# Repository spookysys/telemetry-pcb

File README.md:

# A brain for my rocket

## Features 

* Arduino-compatible
* Adafruit Feather M0 firmware and pinout
* Small size - fits the smallest model rockets (e.g. 26mm diameter)
* Fairly powerful MCU (Atmel ARM M0 at 32MHz)
* GSM/GPRS for telemetry (SIM868)
* GPS for positioning (SIM868)
* 9-DOF Inertial Motion Unit (MPU-9259)
* Altimeter (BMP-280)
* MicroSD for logging
* Integrated usb-port, lipo-charger and power switch

## Adafruit Feather compatibility

* Same pinout as Adafruit Feather M0. An on-board component interfers with D5 (see note).
* MicroSD wired similar to Adalogger M0, but chip-select is on D7 not D4
* Voltage is 3.0 instead of 3.3
* I2C pull-ups are present

Note: If you don't need hardware handshaking on the GSM UART, the D5 pin can be freed up by cutting JP2 on the back of the board.

## Status

Testing in progress

## Credit

Design derived from Adafruit M0 Feather Proto and Adalogger

Adafruit invests time and resources providing this open source design, 
please support Adafruit and open-source hardware by purchasing 
products from Adafruit!

Creative Commons Attribution, Share-Alike license, check license.txt for more information
All text above must be included in any redistribution

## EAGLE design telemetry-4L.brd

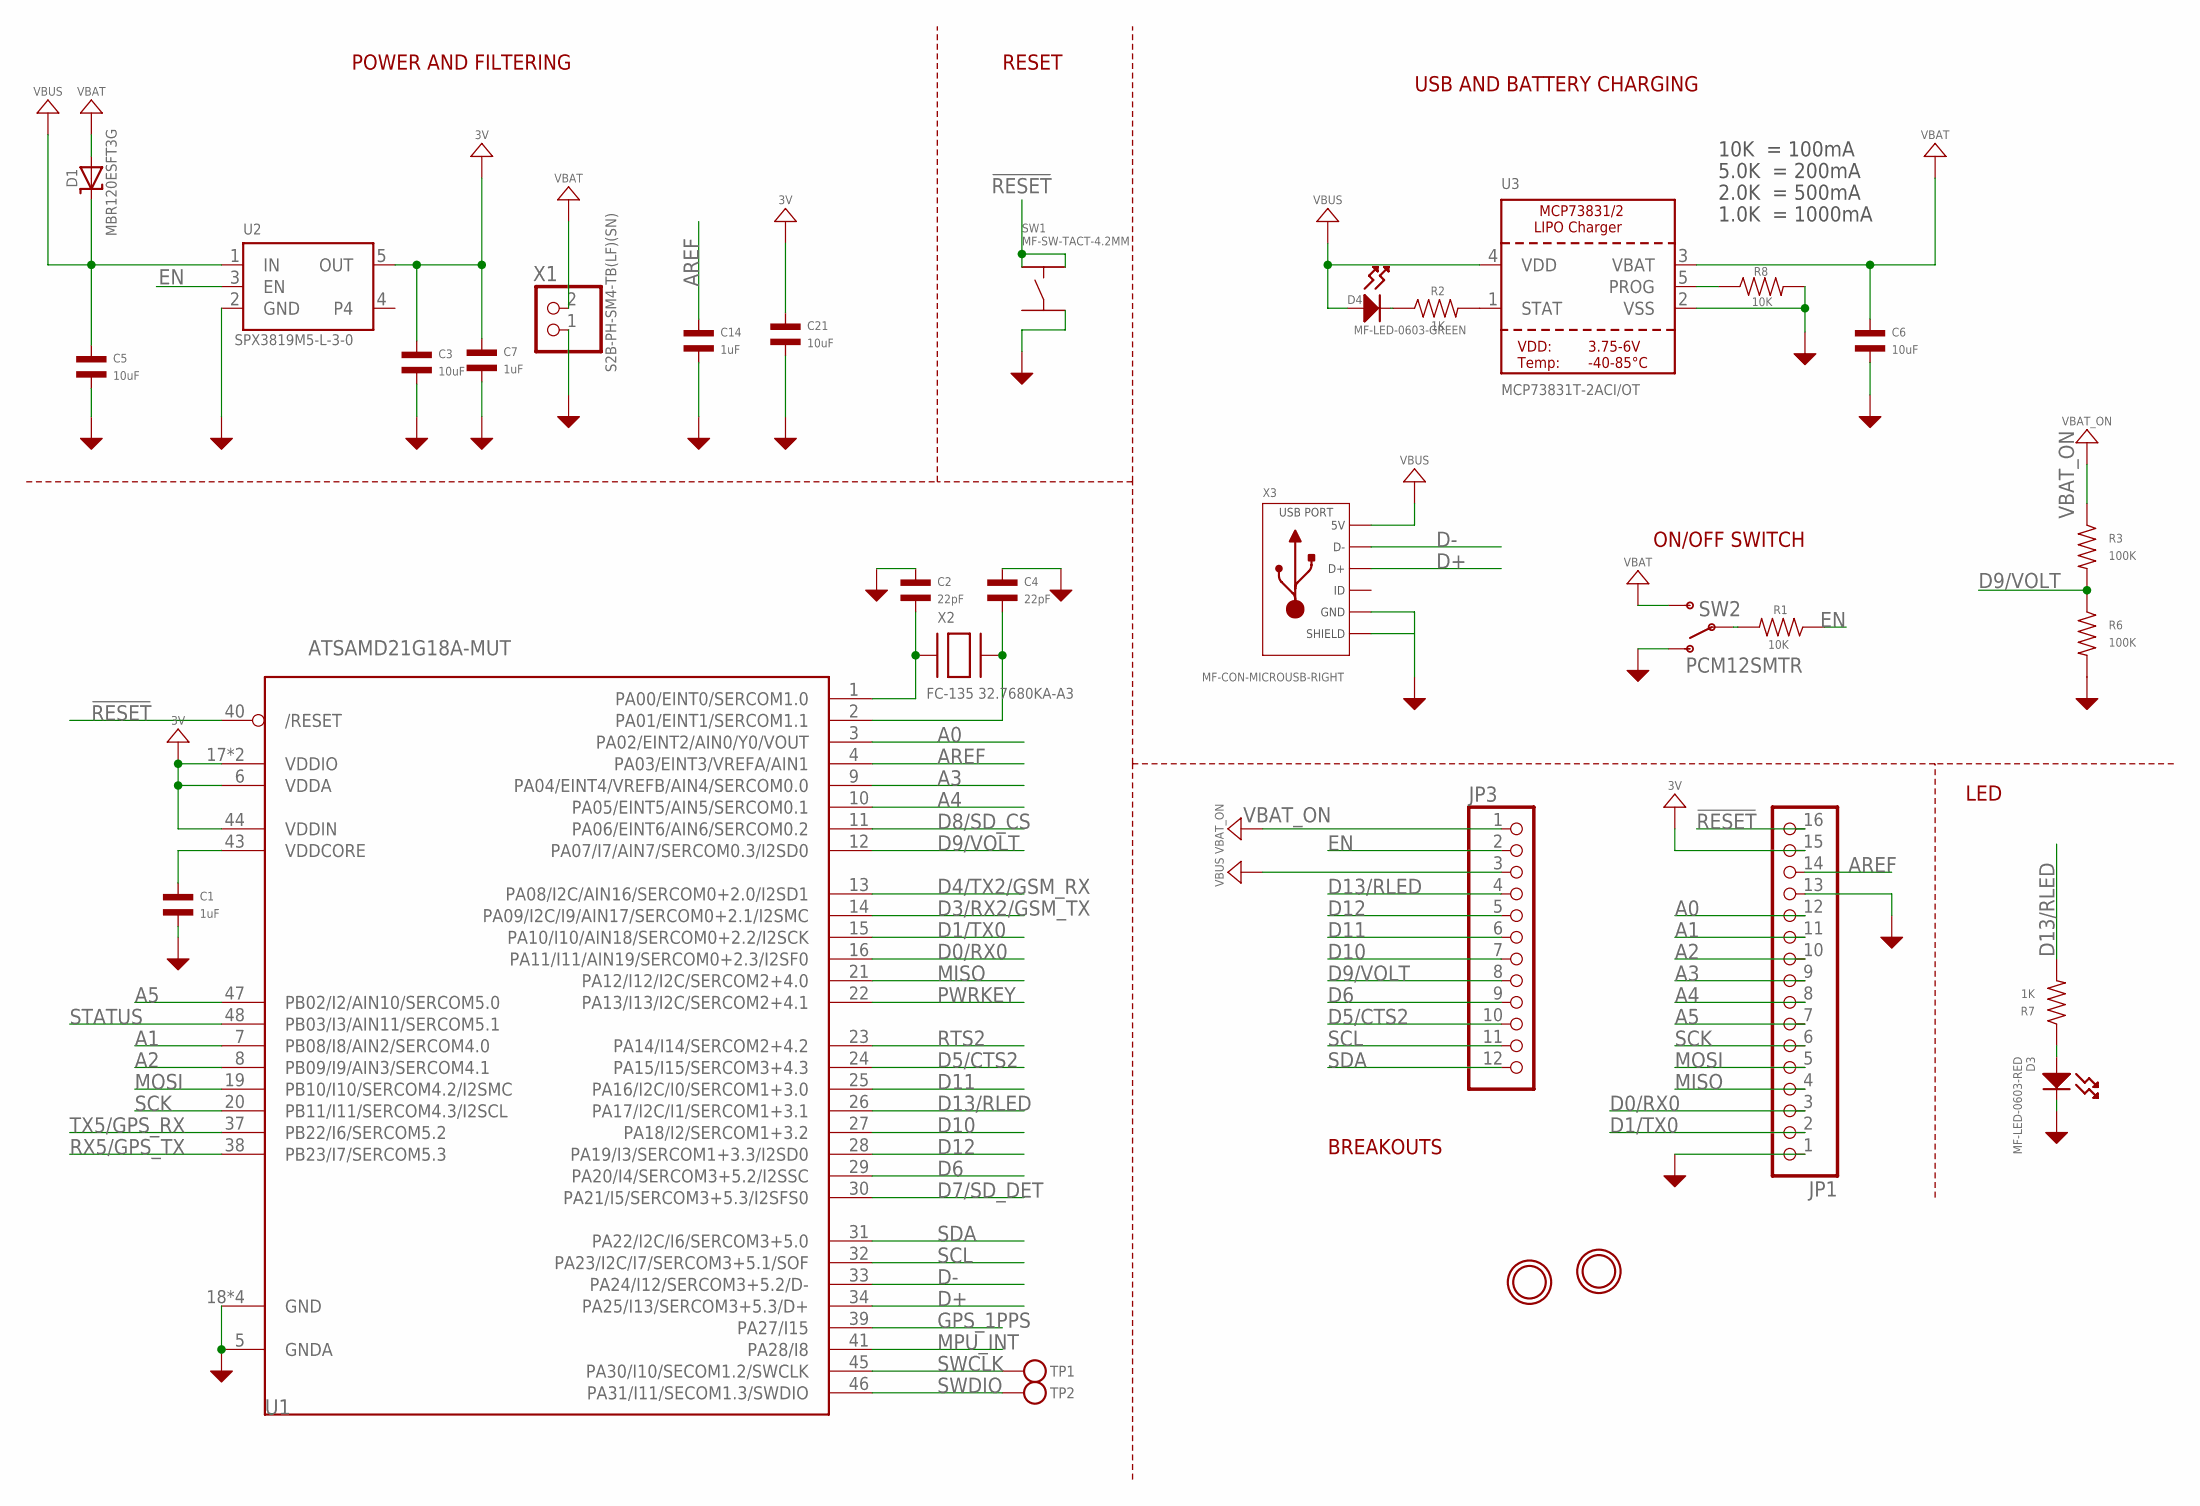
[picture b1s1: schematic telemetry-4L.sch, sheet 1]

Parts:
C1, C7, C14: 1uF; C0402
C2, C4: 22pF; C0402
C3, C5, C6, C21: 10uF; C0603; MPN GRM188R60J106ME47D
D1: MBR120ESFT3G; SOD-123
D3: MF-LED-0603-RED; LED0603
D4: MF-LED-0603-GREEN; LED0603
JP1: HEADER-1X16ROUND; 1X16_ROUND
JP3: HEADER-1X12; 1X12_ROUND
R1, R8: 10K; R0402
R2, R7: 1K; R0402
R3, R6: 100K; R0402
SW1: MF-SW-TACT-4.2MM; TACT4.2MM
SW2: PCM12SMTR; KPS-1290
TP1, TP2: TESTPOINTROUND1.5MM; TESTPOINT_ROUND_1.5MM
U1: ATSAMD21G18A-MUT; TQFN48_7MM
U2: SPX3819M5-L-3-0; SOT23-5
U3: MCP73831T-2ACI/OT; SOT23-5
U$31, U$32: MOUNTINGHOLE2.5; MOUNTINGHOLE_2.5_PLATED
X1: S2B-PH-SM4-TB(LF)(SN); JSTPH2
X2: FC-135 32.7680KA-A3; XTAL3215
X3: MF-CON-MICROUSB-RIGHT; MICROUSB-RIGHT

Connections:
!RESET: JP1.16, SW1.P$1, SW1.P$2, U1.40 (/RESET)
+3V: C3.P$1, C7.P$1, C21.P$1, JP1.15, U1.6 (VDDA), U1.17 (VDDIO), U1.36 (VDDIO), U1.44 (VDDIN), U2.5 (OUT); also elsewhere on the board
A0: JP1.12, U1.3 (PA02/EINT2/AIN0/Y0/VOUT)
A1: JP1.11, U1.7 (PB08/I8/AIN2/SERCOM4.0)
A2: JP1.10, U1.8 (PB09/I9/AIN3/SERCOM4.1)
A3: JP1.9, U1.9 (PA04/EINT4/VREFB/AIN4/SERCOM0.0)
A4: JP1.8, U1.10 (PA05/EINT5/AIN5/SERCOM0.1)
A5: JP1.7, U1.47 (PB02/I2/AIN10/SERCOM5.0)
AREF: C14.P$1, JP1.14, U1.4 (PA03/EINT3/VREFA/AIN1)
D0/RX0: JP1.3, U1.16 (PA11/I11/AIN19/SERCOM0+2.3/I2SF0)
D1/TX0: JP1.2, U1.15 (PA10/I10/AIN18/SERCOM0+2.2/I2SCK)
D3/RX2/GSM_TX: U1.14 (PA09/I2C/I9/AIN17/SERCOM0+2.1/I2SMC); also elsewhere on the board
D4/TX2/GSM_RX: U1.13 (PA08/I2C/AIN16/SERCOM0+2.0/I2SD1); also elsewhere on the board
D5/CTS2: JP3.10, U1.24 (PA15/I15/SERCOM3+4.3); also elsewhere on the board
D6: JP3.9, U1.29 (PA20/I4/SERCOM3+5.2/I2SSC)
D7/SD_DET: U1.30 (PA21/I5/SERCOM3+5.3/I2SFS0); also elsewhere on the board
D8/SD_CS: U1.11 (PA06/EINT6/AIN6/SERCOM0.2); also elsewhere on the board
D9/VOLT: JP3.8, R3.P$2, R6.P$1, U1.12 (PA07/I7/AIN7/SERCOM0.3/I2SD0)
D10: JP3.7, U1.27 (PA18/I2/SERCOM1+3.2)
D11: JP3.6, U1.25 (PA16/I2C/I0/SERCOM1+3.0)
D12: JP3.5, U1.28 (PA19/I3/SERCOM1+3.3/I2SD0)
D13/RLED: JP3.4, R7.P$2, U1.26 (PA17/I2C/I1/SERCOM1+3.1)
D+: U1.34 (PA25/I13/SERCOM3+5.3/D+), X3.3 (D+)
D-: U1.33 (PA24/I12/SERCOM3+5.2/D-), X3.2 (D-)
EN: JP3.2, R1.P$1, U2.3 (EN); also elsewhere on the board
GND: C1.P$2, C2.P$1, C3.P$2, C4.P$1, C5.P$2, C6.P$2, C7.P$2, C14.P$2, C21.P$2, D3.CATHODE, JP1.1, JP1.13, R6.P$2, R8.P$2, SW1.P$4, SW2.O, U1.5 (GNDA), U1.18 (GND), U1.35 (GND), U1.42 (GND), U1.THERMAL (GND), U2.2 (GND), U3.2 (VSS), X1.1, X3.5 (GND), X3.S1 (SLD), X3.S2 (SLD), X3.S3 (SLD), X3.S4 (SLD), X3.S5 (SLD), X3.S6 (SLD); also elsewhere on the board
GPS_1PPS: U1.39 (PA27/I15); also elsewhere on the board
MISO: JP1.4, U1.21 (PA12/I12/I2C/SERCOM2+4.0); also elsewhere on the board
MOSI: JP1.5, U1.19 (PB10/I10/SERCOM4.2/I2SMC); also elsewhere on the board
MPU_INT: U1.41 (PA28/I8); also elsewhere on the board
unnamed: D4.CATHODE, R2.P$1
unnamed: R2.P$2, U3.1 (STAT)
unnamed: R8.P$1, U3.5 (PROG)
unnamed: C2.P$2, U1.1 (PA00/EINT0/SERCOM1.0), X2.P$1
unnamed: C4.P$2, U1.2 (PA01/EINT1/SERCOM1.1), X2.P$2
unnamed: D3.ANODE, R7.P$1
unnamed: R1.P$2, SW2.P
PWRKEY: U1.22 (PA13/I13/I2C/SERCOM2+4.1); also elsewhere on the board
RTS2: U1.23 (PA14/I14/SERCOM2+4.2); also elsewhere on the board
RX5/GPS_TX: U1.38 (PB23/I7/SERCOM5.3); also elsewhere on the board
SCK: JP1.6, U1.20 (PB11/I11/SERCOM4.3/I2SCL); also elsewhere on the board
SCL: JP3.11, U1.32 (PA23/I2C/I7/SERCOM3+5.1/SOF); also elsewhere on the board
SDA: JP3.12, U1.31 (PA22/I2C/I6/SERCOM3+5.0); also elsewhere on the board
STATUS: U1.48 (PB03/I3/AIN11/SERCOM5.1); also elsewhere on the board
SWCLK: TP1.P$1, U1.45 (PA30/I10/SECOM1.2/SWCLK); also elsewhere on the board
SWDIO: TP2.P$1, U1.46 (PA31/I11/SECOM1.3/SWDIO)
TX5/GPS_RX: U1.37 (PB22/I6/SERCOM5.2); also elsewhere on the board
VBAT: C6.P$1, D1.A, SW2.S, U3.3 (VBAT), X1.2; also elsewhere on the board
VBAT_ON: JP3.1, R3.P$1; also elsewhere on the board
VBUS: C5.P$1, D1.C, D4.ANODE, JP3.3, U2.1 (IN), U3.4 (VDD), X3.1 (5V)
VDDCORE: C1.P$1, U1.43 (VDDCORE)

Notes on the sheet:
POWER AND FILTERING
RESET
10K = 100mA
5.0K = 200mA
2.0K = 500mA
1.0K = 1000mA
USB AND BATTERY CHARGING
BREAKOUTS
LED
ON/OFF SWITCH

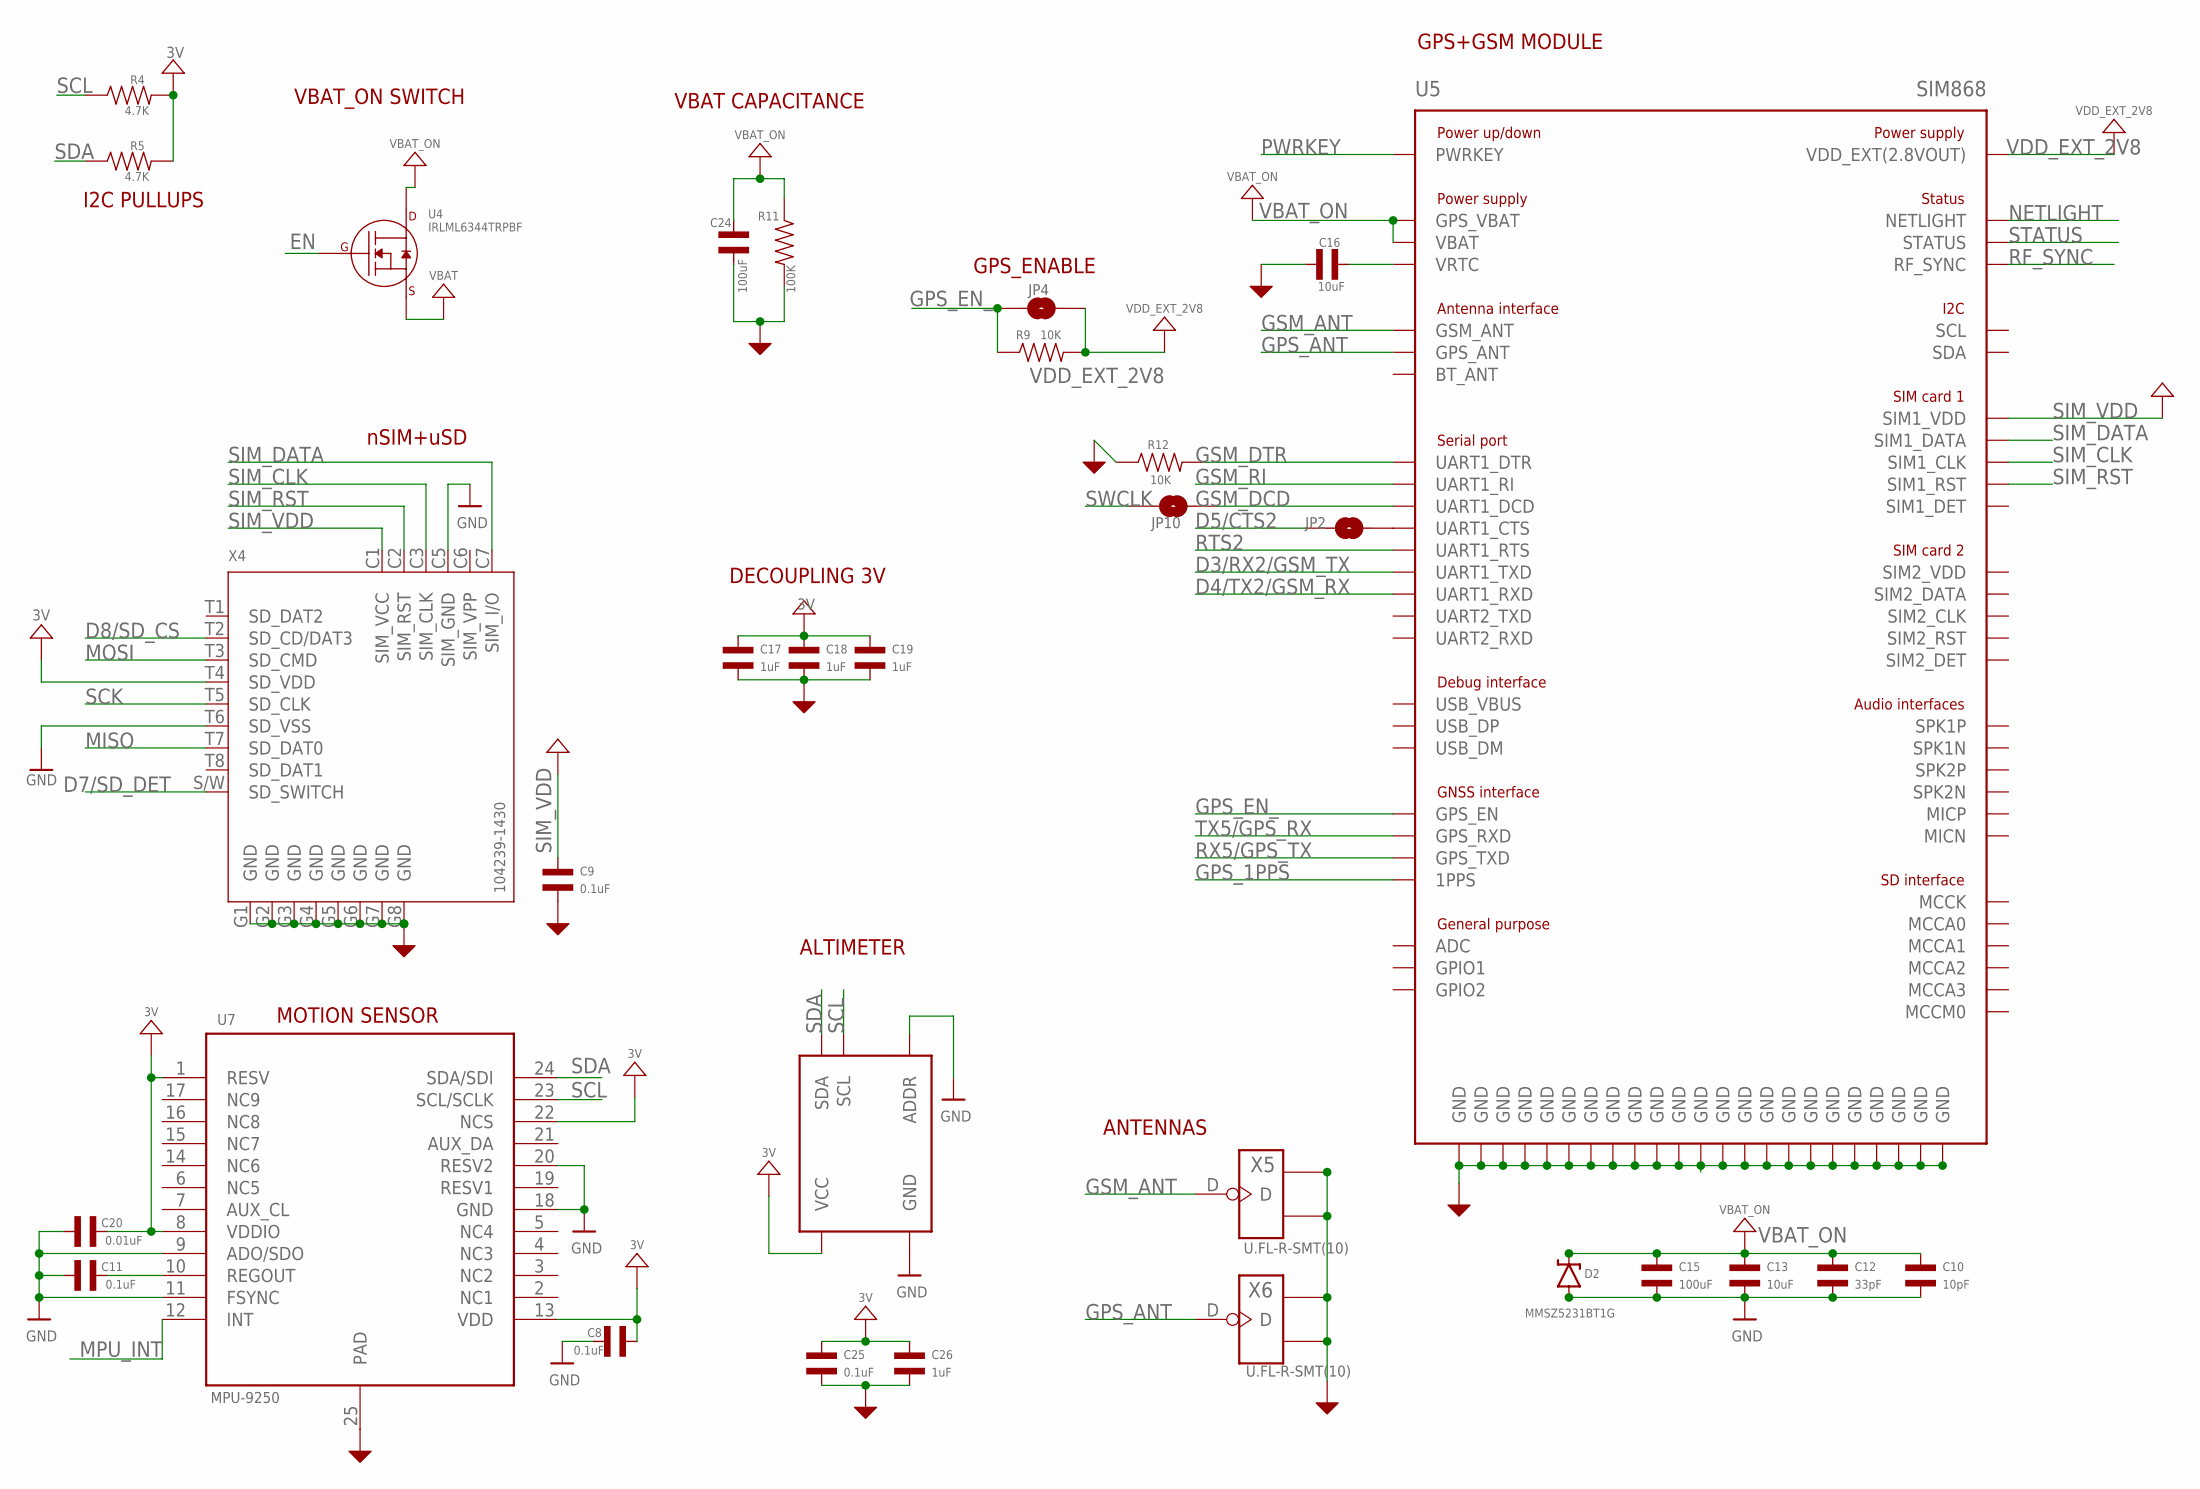
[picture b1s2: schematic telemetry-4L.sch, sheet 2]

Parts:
C8, C9, C11, C25: 0.1uF; C0402
C10: 10pF; C0402; MPN GRM1555C1H100JA01J
C12: 33pF; C0402; MPN GRM1555C1H330JA01D
C13, C16: 10uF; C0603; MPN GRM188R60J106ME47D
C15, C24: 100uF; C1206; MPN CL31A107MQHNNNE
C17, C18, C19, C26: 1uF; C0402
C20: 0.01uF; C0402
D2: MMSZ5231BT1G; SOD-123
JP2, JP4, JP10: JUMPER-PAD-2-NOYES_SILK; PAD-JUMPER-2-NO_YES_SILK
R4, R5: 4.7K; R0402
R9, R12: 10K; R0402
R11: 100K; R0402
U4: IRLML6344TRPBF; SOT-23-3
U5: SIM868; MPN SIM868
U6: BMP280; LGA-8
U7: MPU-9250; LEAD-QFN24
X4: 104239-1430; MOLEX-SD+SIM-104239; MPN 104239-1430
X5, X6: U.FL-R-SMT(10); U-FL3P-SMD-2.6X2.6X1.0MM

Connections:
+3V: C8.P$2, C17.P$1, C18.P$1, C19.P$1, C20.P$2, C25.P$1, C26.P$1, R4.P$2, R5.P$2, U6.P2 (VCC), U6.P6 (VCC), U6.P8 (VCC), U7.1 (RESV), U7.8 (VDDIO), U7.13 (VDD), U7.22 (NCS), X4.T4 (SD_VDD); also elsewhere on the board
D3/RX2/GSM_TX: U5.1_ (UART1_TXD); also elsewhere on the board
D4/TX2/GSM_RX: U5.2_ (UART1_RXD); also elsewhere on the board
D5/CTS2: JP2.1; also elsewhere on the board
D7/SD_DET: X4.S/W (SD_SWITCH); also elsewhere on the board
D8/SD_CS: X4.T2 (SD_CD/DAT3); also elsewhere on the board
EN: U4.P$1 (GATE); also elsewhere on the board
GND: C8.P$1, C9.P$2, C10.P$2, C11.P$1, C12.P$2, C13.P$2, C15.P$2, C16.P$1, C17.P$2, C18.P$2, C19.P$2, C20.P$1, C24.P$2, C25.P$2, C26.P$2, D2.A, R11.P$2, R12.P$1, U5.8_ (GND), U5.13_ (GND), U5.19_ (GND), U5.21_ (GND), U5.27_ (GND), U5.30_ (GND), U5.31_ (GND), U5.33_ (GND), U5.36_ (GND), U5.37_ (GND), U5.45_ (GND), U5.63_ (GND), U5.66_ (GND), U5.67_ (GND), U5.69_ (GND), U5.70_ (GND), U5.71_ (GND), U5.72_ (GND), U5.73_ (GND), U5.74_ (GND), U5.75_ (GND), U5.76_ (GND), U5.77_ (GND), U6.P1 (GND), U6.P5 (ADDR), U6.P7 (GND), U7.9 (ADO/SDO), U7.11 (FSYNC), U7.18 (GND), U7.20 (RESV2), U7.25 (PAD), X4.C5 (SIM_GND), X4.G1 (GND), X4.G2 (GND), X4.G3 (GND), X4.G4 (GND), X4.G5 (GND), X4.G6 (GND), X4.G7 (GND), X4.G8 (GND), X4.T6 (SD_VSS), X5.GND1, X5.GND2, X6.GND1, X6.GND2; also elsewhere on the board
GPS_1PPS: U5.60_ (1PPS); also elsewhere on the board
GPS_ANT: U5.68_ (GPS_ANT), X6.D
GPS_EN_: JP4.1, R9.P$1, U5.59_ (GPS_EN)
GSM_ANT: U5.32_ (GSM_ANT), X5.D
GSM_DCD: JP10.2, U5.5_ (UART1_DCD)
GSM_DTR: R12.P$2, U5.6_ (UART1_DTR)
GSM_RI: U5.7_ (UART1_RI)
MISO: X4.T7 (SD_DAT0); also elsewhere on the board
MOSI: X4.T3 (SD_CMD); also elsewhere on the board
MPU_INT: U7.12 (INT); also elsewhere on the board
unnamed: JP2.2, U5.4_ (UART1_CTS)
unnamed: C11.P$2, U7.10 (REGOUT)
unnamed: C16.P$2, U5.28_ (VRTC)
NETLIGHT: U5.41_ (NETLIGHT)
PWRKEY: U5.39_ (PWRKEY); also elsewhere on the board
RF_SYNC: U5.29_ (RF_SYNC)
RTS2: U5.3_ (UART1_RTS); also elsewhere on the board
RX5/GPS_TX: U5.61_ (GPS_TXD); also elsewhere on the board
SCK: X4.T5 (SD_CLK); also elsewhere on the board
SCL: R4.P$1, U6.P4 (SCL), U7.23 (SCL/SCLK); also elsewhere on the board
SDA: R5.P$1, U6.P3 (SDA), U7.24 (SDA/SDI); also elsewhere on the board
SIM2_VDD: U5.56_ (SIM2_VDD)
SIM_CLK: U5.16_ (SIM1_CLK), X4.C3 (SIM_CLK)
SIM_DATA: U5.15_ (SIM1_DATA), X4.C7 (SIM_I/O)
SIM_RST: U5.17_ (SIM1_RST), X4.C2 (SIM_RST)
SIM_VDD: C9.P$1, U5.18_ (SIM1_VDD), X4.C1 (SIM_VCC)
STATUS: U5.42_ (STATUS); also elsewhere on the board
SWCLK: JP10.1; also elsewhere on the board
TX5/GPS_RX: U5.62_ (GPS_RXD); also elsewhere on the board
USB_VBUS: U5.24_ (USB_VBUS)
VBAT: U4.P$2 (SOURCE); also elsewhere on the board
VBAT_ON: C10.P$1, C12.P$1, C13.P$1, C15.P$1, C24.P$1, D2.C, R11.P$1, U4.P$3 (DRAIN), U5.34_ (GPS_VBAT), U5.35_ (VBAT); also elsewhere on the board
VDD_EXT_2V8: JP4.2, R9.P$2, U5.40_ (VDD_EXT(2.8VOUT))

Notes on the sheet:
ALTIMETER
nSIM+uSD
I2C PULLUPS
GPS+GSM MODULE
ANTENNAS
GPS_ENABLE
VBAT_ON SWITCH
DECOUPLING 3V
MOTION SENSOR
VBAT CAPACITANCE

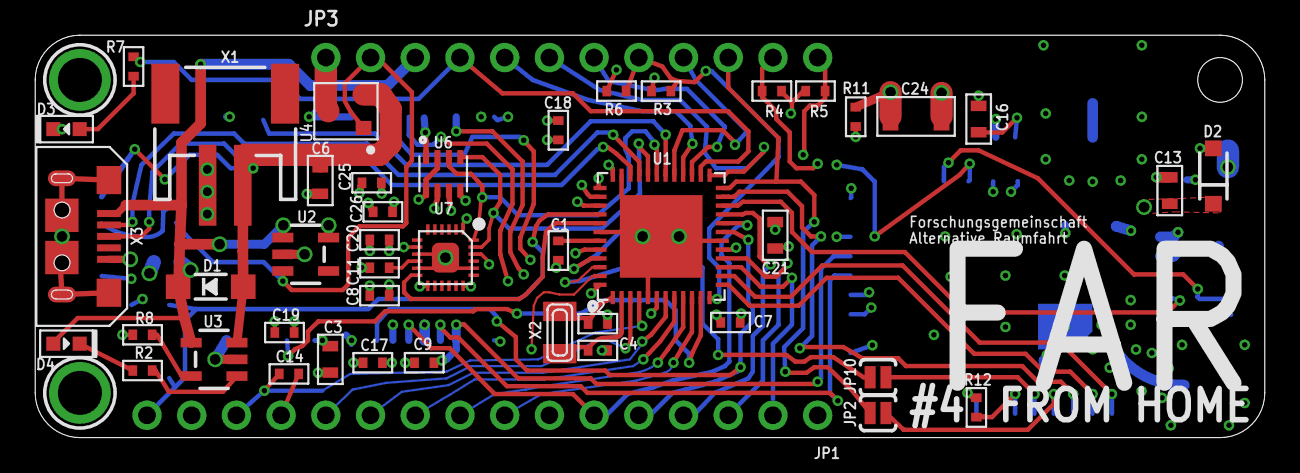
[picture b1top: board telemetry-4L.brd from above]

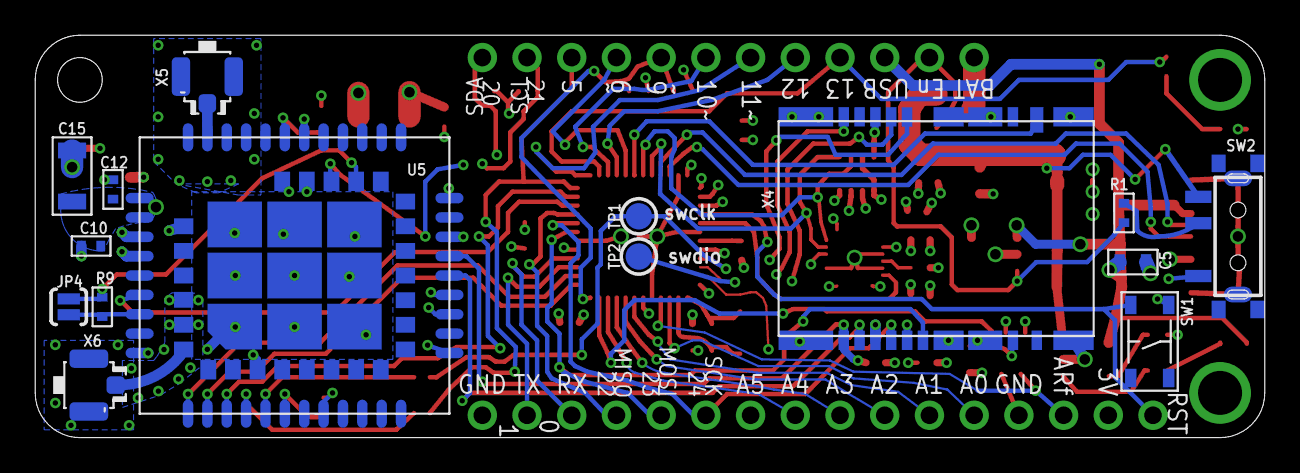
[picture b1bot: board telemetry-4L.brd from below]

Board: 4 copper layers, 69.8 x 22.9 mm, 63 parts (15 on the bottom side), 64 nets.

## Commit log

2016-08-12 First version i Please enter the commit message for your changes. Lines starting
2016-08-12 Added DRU and CAM files that I'm using (from SEEED)
2016-08-12 Fixed unconnected microsd chip-select
2016-08-12 Prev. commit was faulty, only half fixed Also fixed a number of ERC/DRC issues
2016-08-12 Placed pad for SD_DET
2016-08-13 Added libraries
2016-08-13 Added bypass capacitors ++
2016-08-13 More bypass for SIM and SD
2016-08-13 Removed bRestrict pads from SD/SIM connector
2016-08-13 Changed LEDs to Seeed ++
2016-08-13 Swapped switch for Seeed version
2016-08-13 Swapped Micro-USB connector for Seeed
2016-08-13 Swapped some capacitors
2016-08-13 Added BOM csv file (hand made) for seeed
2016-08-13 Swapped obsolete part BMP180 for BMP280
2016-08-13 Improved readme, renamed bom-fixed.csv to bom-seeed.csv
2016-08-13 Aesthetic improvements to placement on backside
2016-08-13 changed all measurements to be in inches
2016-08-13 a ground via was unconnected
2016-08-14 Made lots of tweaks!
2016-08-15 LOTS of tweaks. No more 403s.
2016-08-15 Swapped USB port to deegou
2016-08-15 added seeed MPN as attribute on Deegou USB port
2016-08-15 removed wattages in resistor values
2016-08-15 Did I do anything at all?
2016-08-16 Moved things around to improve capacitor placement
2016-08-16 Added BOM for Deegou Note that bom-seeed is outdated at this point
2016-08-16 Added some more connections to improve ground covg
2016-08-23 Minor adjustments
2016-08-23 killed out of date bom-seed, added some ulps
2016-08-23 fixed a short circuit introduced when changing the 100uF caps to ceramic
2016-08-23 added Macrofab dru-file
2016-08-23 Switched Tantanum AVX-B caps with Ceramic C1206
2016-08-23 updated bom-deegou to reflect now using only Ceramic caps
2016-09-01 Shrunk the board some mils horizontally
2016-09-01 Made it even a tiny bit shorter
2016-10-07 Tweaked GPS antenna trace
2016-10-08 Added shorter board with some comps on backside
2016-10-08 Small fixes
2016-10-09 Updated for MacroFab
2016-10-09 Connected GPS_EN to 2V8 by jumper
2016-10-09 Fixed some DRC failures
2016-10-09 Deleted long board version
2016-10-09 Added logo to back
2016-10-10 Cleanups
2016-10-10 Started new 4-layer version
2016-10-11 working on new board
2016-10-12 Working on 4-layer version
2016-10-13 Last edit before switching Bosch -> Invensense MPU
2016-10-13 Switched to MPU-9250 IMU
2016-10-13 Everything placed
2016-10-13 Power and ground: routed
2016-10-13 Some work on routing
2016-10-16 Worked on it
2016-10-16 Put Sim868 on backside!
2016-10-17 Added a second JP2 socket for servo output
2016-10-17 Moved power mosfet out
2016-10-17 Connected servo power in schematic
2016-10-17 All done
2016-10-17 Killed 2-layer version
2016-10-17 Made prettier
2016-10-17 Prettification
2016-10-18 Seems ok now
2016-10-18 fixed some names
2016-10-18 Moved power mosfet back upstream
2016-10-18 tweaks
2016-10-19 Changed GPS_EN pin to SERVO_EN, so I can arm at a distance
2016-10-19 Added MPR and POPULATE attributes - didnt seem to do anything though
2016-10-19 Added a 100uF cap to 5V output
2016-10-30 Added a pull-down to 5V enable signal
2016-10-30 aesthetics
2016-10-30 fixed some unconnected airwires (important fix)
2016-10-31 Input capacitor for 5V regulator was wrong value
2016-10-31 Added wind-down resistor to 5V output Killed cutout under MPU, as I don't know if it will work
2016-10-31 Made some more space around the 5V supply
2016-10-31 added resistor to ground on DTR, as per SIM800 Serial App Note
2016-11-10 Moved battery connector back a tad, as it got in the way in my current prototype
2016-11-12 Moved both power plugs back a tad
2016-11-15 Added connection to DCD shared with SWCLK - might be needed for FTP and similar
    Try using FTP and if not needed, kill this again
2016-11-15 Fixed the PCB to reflect last change in schematic
2016-11-15 Logo aesthetics - added #2
2016-11-15 Fixed a problem with overlapping diode and cleaned up files
2016-11-15 More fixes of overlapping components
2016-11-23 Connected 1PPS via jumper made CTS jumper default NO
2016-11-25 some automatic changes to project file::::
2016-12-06 Moved "forsch..." to the backside (correctly)
2016-12-23 Increased margins in middle part of board
2016-12-23 Improvements on the right side
2016-12-23 Fixed bigger margins on the right side¨ Only left side remains
2016-12-23 Misc improvements
2016-12-24 fixed more margins Remember: Have a look at A5 trace and via
2016-12-24 moved sd slot to the left, making more room for a5
2016-12-24 Finished layout fixed all obvious errors
2016-12-25 attempt to put a right angle reset button
2016-12-25 Revert "attempt to put a right angle reset button"
    This reverts commit 0c88159f70d3469a455fb55c16ca82abb05fa745.
2016-12-25 small fixes (some very important)
2016-12-25 Margins around lower antenna
2016-12-25 Moved names around
2016-12-25 Dont know, but this went to ccreate an order
2017-01-26 Killed "Servo Power 2" components
2017-01-26 Swapped power FET with the one used by adafruit - Noticed the old one was the wrong way around!!
2017-01-26 Revert "Swapped power FET with the one used by adafruit"
    This reverts commit fb89b7665746a5f81bf27fb940dbf5a3e6cbfe7e.
2017-01-26 Swapped Power MOSFET Source and Drain so it's correct
2017-01-26 Removed 5V power supply. This can be on shield!
2017-01-26 Ryddet litt i tracene
2017-01-26 Hooked GPS_1PPS to a normal pin, instead of SWDIO
2017-01-26 Updated libraries - short circuit in usb plug should be gone. Also moved USB and switch a tad to make it stick better

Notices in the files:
parts and their libraries:
microbuilder: This work is placed in the public domain, and may be freely used for commercial and non-commercial work with the following conditions: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
SparkFun-Passives: Licensing: Creative Commons ShareAlike 4.0 International - https://creativecommons.org/licenses/by-sa/4.0
